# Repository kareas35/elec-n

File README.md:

# elec-n
Elektronik eğitim ve hesaplayıcılar sitesi

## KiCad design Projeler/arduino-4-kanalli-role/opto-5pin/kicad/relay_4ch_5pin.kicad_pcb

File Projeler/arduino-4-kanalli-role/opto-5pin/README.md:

# 4 Röleli Arduino Devresi — V2 / 5 Pinli (kullanıcı pin haritası)

Klasör: `C:\SalonAsistan\yatirim_takip\devre_4role_5pin_duzeltilmis`

## Pin haritası (onaylanan düzen)

**J1 — Yeni 5 pinli kontrol soketi**

| Pin | İsim | Bağlantı |
|---|---|---|
| 1 | GND | Arduino GND |
| 2 | IN1 | Arduino **D4** |
| 3 | IN2 | Arduino **D5** |
| 4 | IN3 | Arduino **D6** |
| 5 | IN4 | Arduino **D7** |

**J2 — Tek röle besleme girişi**

| Pin | Bağlantı |
|---|---|
| 1 | Harici **+5 V DC** |
| 2 | GND |

J1'de **5V yoktur**. Arduino yalnızca USB'den beslenir. J2'den gelen +5V yalnızca röle bobinlerini besler; Arduino'ya verilmez. Eski 6 pinli sürümde +5V header'daydı ve iki 5V birbirine karışıyordu; bu sürümde o pin kaldırıldı.

## Devre özeti (her kanal)

- Arduino `D4–D7` → **1 kΩ** → PC817 giriş LED'i (pin 1) → pin 2 → `GND_A`
- PC817 çıkışı: pin 4 → `+5V_B`, pin 3 → `B{k}` → **4k7** → `GND_B`
- `B{k}` → **BC547** tabanı; kollektör → röle bobini → `+5V_B`
- Bobin üzerinde **1N4148** flyback diyot
- Röle kontağı **COM / NO** → yük terminali `J{k+2}` (J3–J6)
- Filtre: J2 `+5V_B` için **100 µF + 100 nF**
- Mantık: Arduino `HIGH` → röle çekilir → COM-NO kapanır
- PC817 optokuplörleri sayesinde `GND_A` (Arduino) ve `GND_B` (röle) ayrıdır; PCB'de **X = 64.5–67.0 mm** bakırsız bariyer vardır.

> Wokwi'de optokuplör bileşeni olmadığı için simülasyonda GND'ler ortak gösterilmiştir. Gerçek PCB'de ayrıdır.

## Dosyalar

| Yol | İçerik |
|---|---|
| `kicad/relay_4ch_5pin.kicad_pro` | KiCad 10 projesi |
| `kicad/relay_4ch_5pin.kicad_sch` | Şema (J1 5 pin, J2 tek besleme) |
| `kicad/relay_4ch_5pin.kicad_pcb` | 2 katman PCB, izolasyon bariyerli |
| `kicad/design.py`, `gen_sch.py`, `gen_pcb.py` | Tek kaynaklı üretim betikleri |
| `kicad/cikti/sema.png`, `.svg`, `.pdf` | Şema çıktıları |
| `kicad/cikti/pcb.png`, `.svg` | PCB görünümü |
| `kicad/cikti/3d_ust.png`, `3d_izometrik.png` | 3B render'lar |
| `kicad/cikti/bom.csv` | Malzeme listesi |
| `sim/sketch.ino` | Arduino kodu (D4–D7) |
| `sim/diagram.json`, `wokwi.toml` | Wokwi simülasyon projesi |
| `sim/simulasyon.html` | İnternetsiz, tarayıcıda çalışan canlı simülasyon |
| `sim/build_sim.py` | `sketch.ino` → HTML içine gömer |
| `gorsel/index.html` | Tüm çıktıların görsel özet sayfası |
| `gorsel/varliklar/` | Galerinin kullandığı şema/PCB/3B/simülasyon kopyaları |
| `gorsel/hazirla.py` | Kaynak dosyaları `gorsel/varliklar/` içine kopyalar |
| `gorsel/simulasyon.gif` | Çalışan simülasyonun kaydı |

## Simülasyonu çalıştırma

1. **Tarayıcı (internetsiz):** `sim\simulasyon.html` dosyasına çift tıkla. `sketch.ino` içine gömülü olduğu için aynı kod çalışır. Hız etiketine tıklayarak 1/2/4/8x arasında geçiş yapılır.
2. **Wokwi:** `https://wokwi.com` → *New Arduino Uno Project* → `diagram.json` ve `sketch.ino` içeriklerini yapıştır → *Start simulation*.
3. **Görsel özet:** `gorsel\index.html` dosyasını aç.

## Arduino seri komutları

| Komut | Etki |
|---|---|
| `a` | 4 röleyi aç |
| `k` | 4 röleyi kapat |
| `1`–`4` | İlgili röleyi aç/kapat (toggle) |
| `s` | Durumları yazdır |

Otomatik demo: 4 açık (1.5 s) → 4 kapalı (0.9 s) → sırayla R1…R4 (0.6 s açık / 0.3 s kapalı) → tekrar.

## Doğrulama sonuçları

- **ERC:** 0 hata, 0 uyarı
- **DRC:** 0 ihlal
- **Router:** 32 bağlantı / 32 başarılı
- **Arduino CLI:** `arduino:avr:uno` derlemesi başarılı (3310 B flash, 224 B RAM)
- **Wokwi:** `diagram.json` geçerli, 18 parça / 32 bağlantı
- **Simülasyon:** `simulasyon.gif` ve `gorsel/sim_durum_*.png` kayıtları

## Yeniden üretim

```powershell
cd C:\SalonAsistan\yatirim_takip\devre_4role_5pin_duzeltilmis
python kicad\gen_sch.py
& 'C:\Program Files\KiCad\10.0\bin\python.exe' kicad\gen_pcb.py
& 'C:\Program Files\KiCad\10.0\bin\kicad-cli.exe' sch erc --severity-all -o kicad\erc.json --format json kicad\relay_4ch_5pin.kicad_sch
& 'C:\Program Files\KiCad\10.0\bin\kicad-cli.exe' pcb drc --severity-all -o kicad\drc.json --format json kicad\relay_4ch_5pin.kicad_pcb
python sim\build_sim.py
python sim\animasyon.py
python gorsel\hazirla.py
```

> `gorsel\index.html` dosyası şema/PCB/3B görselleri ile canlı simülasyonu kendi `varliklar\` alt klasöründen okur; dosyalar değiştiğinde `python gorsel\hazirla.py` komutunu çalıştır.

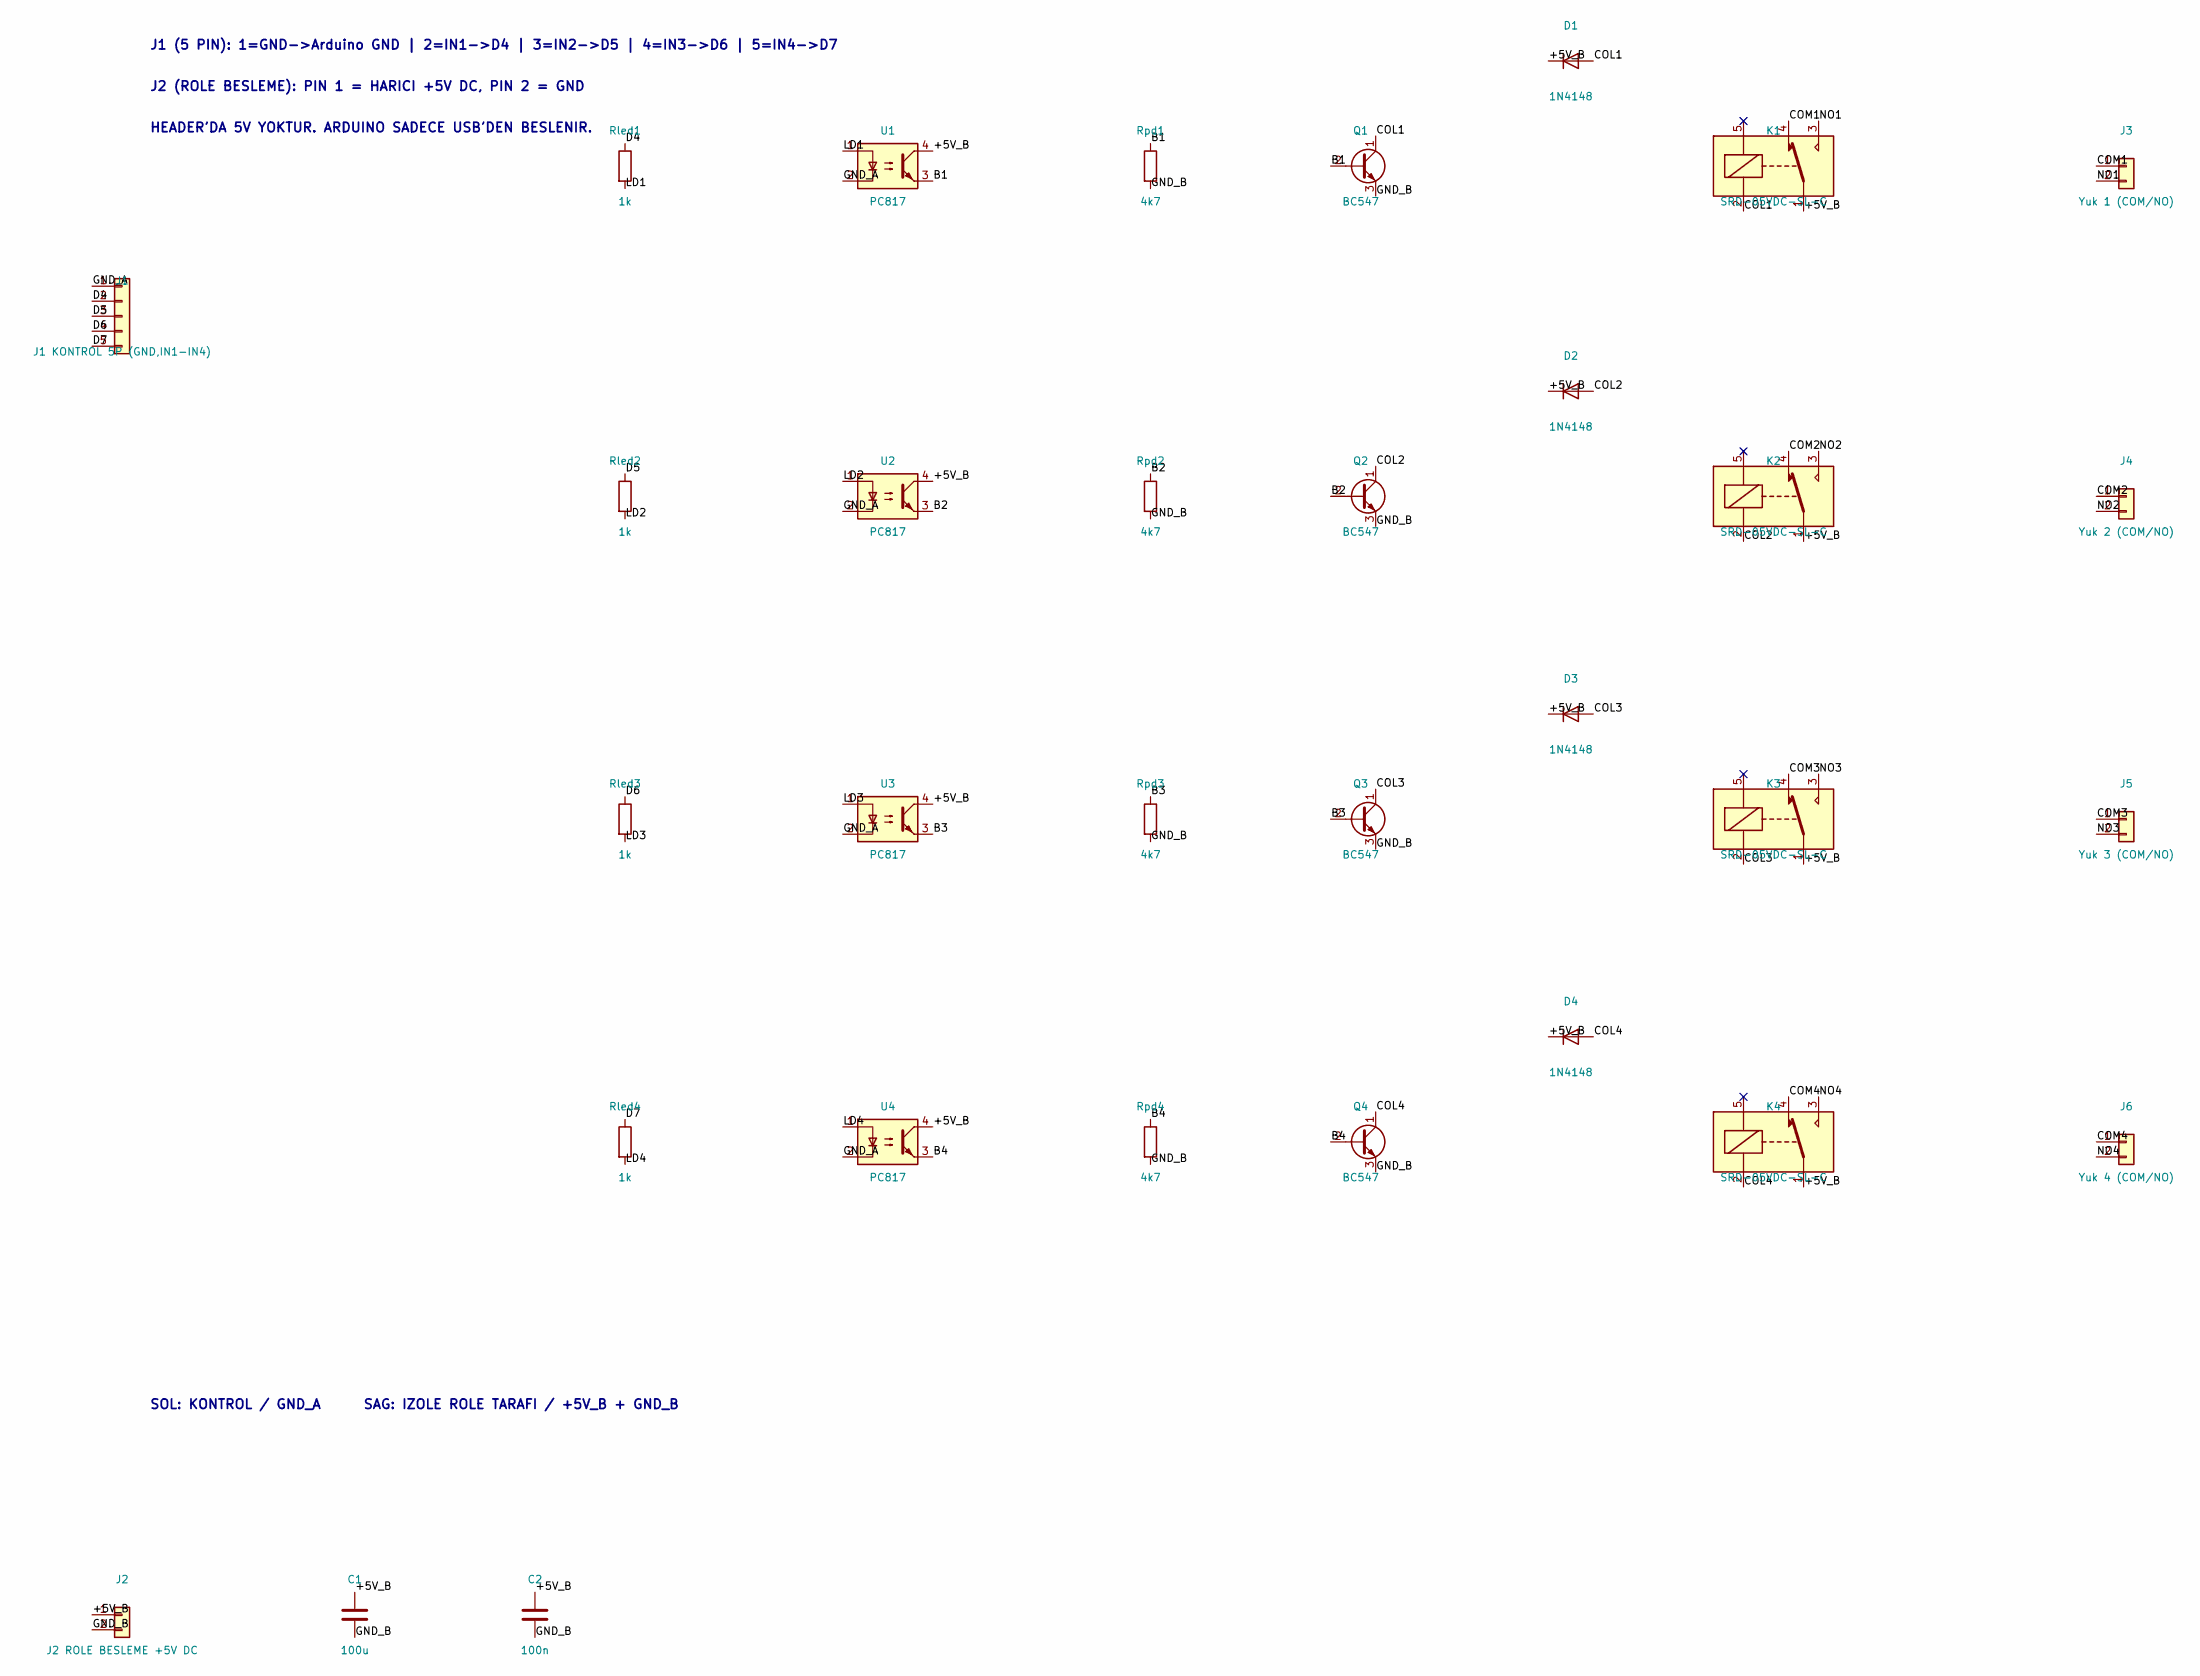
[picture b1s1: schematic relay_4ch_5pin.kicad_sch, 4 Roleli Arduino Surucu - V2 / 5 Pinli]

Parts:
C1: 100u; CP_Radial_D6.3mm_P2.50mm
C2: 100n; C_Disc_D5.0mm_W2.5mm_P5.00mm
D1, D2, D3, D4: 1N4148; D_DO-41_SOD81_P10.16mm_Horizontal
J1: J1 KONTROL 5P (GND,IN1-IN4); PinHeader_1x05_P2.54mm_Vertical
J2: J2 ROLE BESLEME +5V DC; TerminalBlock_Phoenix_MKDS-1,5-2-5.08_1x02_P5.08mm_Horizont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
J3: Yuk 1 (COM/NO); TerminalBlock_Phoenix_MKDS-1,5-2-5.08_1x02_P5.08mm_Horizont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
J4: Yuk 2 (COM/NO); TerminalBlock_Phoenix_MKDS-1,5-2-5.08_1x02_P5.08mm_Horizont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
J5: Yuk 3 (COM/NO); TerminalBlock_Phoenix_MKDS-1,5-2-5.08_1x02_P5.08mm_Horizont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
J6: Yuk 4 (COM/NO); TerminalBlock_Phoenix_MKDS-1,5-2-5.08_1x02_P5.08mm_Horizont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
K1, K2, K3, K4: SRD-05VDC-SL-C; Relay_SPDT_SANYOU_SRD_Series_Form_C
Q1, Q2, Q3, Q4: BC547; TO-92_Inline
Rled1, Rled2, Rled3, Rled4: 1k; R_Axial_DIN0207_L6.3mm_D2.5mm_P10.16mm_Horizontal
Rpd1, Rpd2, Rpd3, Rpd4: 4k7; R_Axial_DIN0207_L6.3mm_D2.5mm_P10.16mm_Horizontal
U1, U2, U3, U4: PC817; DIP-4_W7.62mm

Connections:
+5V_B: C1.1, C2.1, D1.1 (K), D2.1 (K), D3.1 (K), D4.1 (K), J2.1, K1.1, K2.1, K3.1, K4.1, U1.4, U2.4, U3.4, U4.4
B1: Q1.2 (B), Rpd1.1, U1.3
B2: Q2.2 (B), Rpd2.1, U2.3
B3: Q3.2 (B), Rpd3.1, U3.3
B4: Q4.2 (B), Rpd4.1, U4.3
COL1: D1.2 (A), K1.2, Q1.1 (C)
COL2: D2.2 (A), K2.2, Q2.1 (C)
COL3: D3.2 (A), K3.2, Q3.1 (C)
COL4: D4.2 (A), K4.2, Q4.1 (C)
COM1: J3.1, K1.4
COM2: J4.1, K2.4
COM3: J5.1, K3.4
COM4: J6.1, K4.4
D4: J1.2, Rled1.1
D5: J1.3, Rled2.1
D6: J1.4, Rled3.1
D7: J1.5, Rled4.1
GND_A: J1.1, U1.2, U2.2, U3.2, U4.2
GND_B: C1.2, C2.2, J2.2, Q1.3 (E), Q2.3 (E), Q3.3 (E), Q4.3 (E), Rpd1.2, Rpd2.2, Rpd3.2, Rpd4.2
LD1: Rled1.2, U1.1
LD2: Rled2.2, U2.1
LD3: Rled3.2, U3.1
LD4: Rled4.2, U4.1
NC1: K1.5
NC2: K2.5
NC3: K3.5
NC4: K4.5
NO1: J3.2, K1.3
NO2: J4.2, K2.3
NO3: J5.2, K3.3
NO4: J6.2, K4.3

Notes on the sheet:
J1 (5 PIN): 1=GND->Arduino GND | 2=IN1->D4 | 3=IN2->D5 | 4=IN3->D6 | 5=IN4->D7
J2 (ROLE BESLEME): PIN 1 = HARICI +5V DC, PIN 2 = GND
HEADER'DA 5V YOKTUR. ARDUINO SADECE USB'DEN BESLENIR.
SOL: KONTROL / GND_A SAG: IZOLE ROLE TARAFI / +5V_B + GND_B

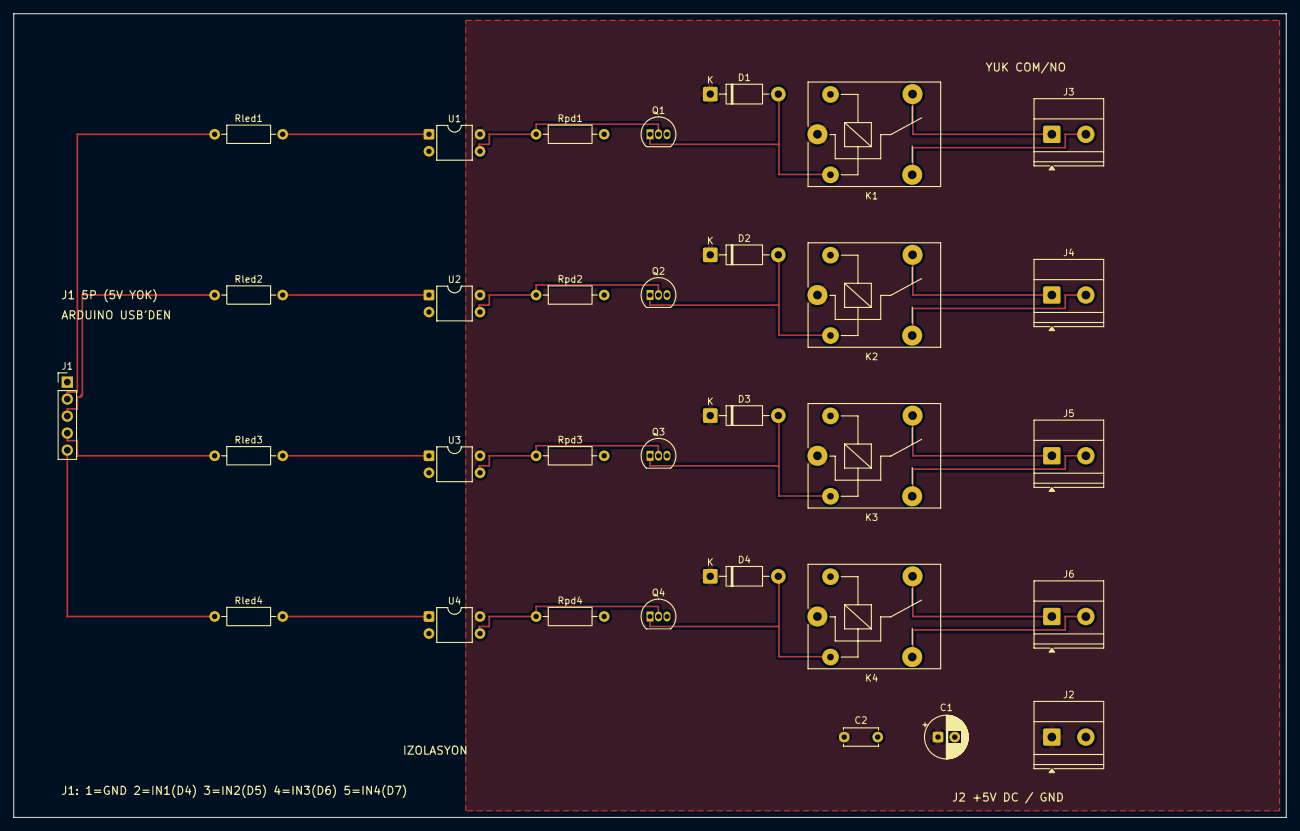
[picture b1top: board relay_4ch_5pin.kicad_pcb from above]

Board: 2 copper layers, 190.0 x 120.0 mm, 32 parts (0 on the bottom side), 27 nets.

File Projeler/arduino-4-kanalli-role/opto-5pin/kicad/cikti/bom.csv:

"Refs","Value","Footprint","Qty","DNP"
"C1","100u","Capacitor_THT:CP_Radial_D6.3mm_P2.50mm","1",""
"C2","100n","Capacitor_THT:C_Disc_D5.0mm_W2.5mm_P5.00mm","1",""
"D1","1N4148","Diode_THT:D_DO-41_SOD81_P10.16mm_Horizontal","1",""
"D2","1N4148","Diode_THT:D_DO-41_SOD81_P10.16mm_Horizontal","1",""
"D3","1N4148","Diode_THT:D_DO-41_SOD81_P10.16mm_Horizontal","1",""
"D4","1N4148","Diode_THT:D_DO-41_SOD81_P10.16mm_Horizontal","1",""
"J1","J1 KONTROL 5P (GND,IN1-IN4)","Connector_PinHeader_2.54mm:PinHeader_1x05_P2.54mm_Vertical","1",""
"J2","J2 ROLE BESLEME +5V DC","TerminalBlock_Phoenix:TerminalBlock_Phoenix_MKDS-1,5-2-5.08_1x02_P5.08mm_Horizontal","1",""
"J3","Yuk 1 (COM/NO)","TerminalBlock_Phoenix:TerminalBlock_Phoenix_MKDS-1,5-2-5.08_1x02_P5.08mm_Horizontal","1",""
"J4","Yuk 2 (COM/NO)","TerminalBlock_Phoenix:TerminalBlock_Phoenix_MKDS-1,5-2-5.08_1x02_P5.08mm_Horizontal","1",""
"J5","Yuk 3 (COM/NO)","TerminalBlock_Phoenix:TerminalBlock_Phoenix_MKDS-1,5-2-5.08_1x02_P5.08mm_Horizontal","1",""
"J6","Yuk 4 (COM/NO)","TerminalBlock_Phoenix:TerminalBlock_Phoenix_MKDS-1,5-2-5.08_1x02_P5.08mm_Horizontal","1",""
"K1","SRD-05VDC-SL-C","Relay_THT:Relay_SPDT_SANYOU_SRD_Series_Form_C","1",""
"K2","SRD-05VDC-SL-C","Relay_THT:Relay_SPDT_SANYOU_SRD_Series_Form_C","1",""
"K3","SRD-05VDC-SL-C","Relay_THT:Relay_SPDT_SANYOU_SRD_Series_Form_C","1",""
"K4","SRD-05VDC-SL-C","Relay_THT:Relay_SPDT_SANYOU_SRD_Series_Form_C","1",""
"Q1","BC547","Package_TO_SOT_THT:TO-92_Inline","1",""
"Q2","BC547","Package_TO_SOT_THT:TO-92_Inline","1",""
"Q3","BC547","Package_TO_SOT_THT:TO-92_Inline","1",""
"Q4","BC547","Package_TO_SOT_THT:TO-92_Inline","1",""
"Rled1","1k","Resistor_THT:R_Axial_DIN0207_L6.3mm_D2.5mm_P10.16mm_Horizontal","1",""
"Rled2","1k","Resistor_THT:R_Axial_DIN0207_L6.3mm_D2.5mm_P10.16mm_Horizontal","1",""
"Rled3","1k","Resistor_THT:R_Axial_DIN0207_L6.3mm_D2.5mm_P10.16mm_Horizontal","1",""
"Rled4","1k","Resistor_THT:R_Axial_DIN0207_L6.3mm_D2.5mm_P10.16mm_Horizontal","1",""
"Rpd1","4k7","Resistor_THT:R_Axial_DIN0207_L6.3mm_D2.5mm_P10.16mm_Horizontal","1",""
"Rpd2","4k7","Resistor_THT:R_Axial_DIN0207_L6.3mm_D2.5mm_P10.16mm_Horizontal","1",""
"Rpd3","4k7","Resistor_THT:R_Axial_DIN0207_L6.3mm_D2.5mm_P10.16mm_Horizontal","1",""
"Rpd4","4k7","Resistor_THT:R_Axial_DIN0207_L6.3mm_D2.5mm_P10.16mm_Horizontal","1",""
"U1","PC817","Package_DIP:DIP-4_W7.62mm","1",""
"U2","PC817","Package_DIP:DIP-4_W7.62mm","1",""
"U3","PC817","Package_DIP:DIP-4_W7.62mm","1",""
"U4","PC817","Package_DIP:DIP-4_W7.62mm","1",""

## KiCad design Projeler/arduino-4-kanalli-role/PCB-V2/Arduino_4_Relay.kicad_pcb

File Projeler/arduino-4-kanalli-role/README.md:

# 4 Kanallı Arduino Röle Kartı

Arduino Uno ile kontrol edilen, ULN2003A sürücülü, 5 V bobinli 4 kanallı röle kartı.
Şema, PCB, 3B görünüm, Gerber/drill, firmware, sayısal simülasyon ve SimulIDE
projesi bu klasörde birlikte bulunur.

> **Güvenlik — yalnızca düşük gerilimli eğitim:**
> Bu PCB'nin 230 V şebeke güvenliği doğrulanmamıştır.
> Şebeke gerilimi bağlamayın. Kontak yolları 0,5 mm'dir;
> güvenli akım kapasitesi henüz doğrulanmamıştır.
> Röleleri Arduino 5 V pininden beslemeyin.
> Harici, regüle 5 V DC kaynak kullanın.
> J2-1: +5 V, J2-2: GND.
> Arduino ve röle kartının GND bağlantısı ortak olmalıdır.
> J1-1 ve J2-1 aynı +5 V hattındadır.
> Harici besleme kullanırken J1-1'i Arduino 5 V pinine
> BAĞLAMAYIN. Mevcut PCB yanlış bağlantıyı engellemez.

## Donanım özeti

| Öğe | Değer / bağlantı |
|---|---|
| Besleme | 5 V DC. 4 röle aynı anda açıksa harici 5 V / 2 A önerilir. |
| Sürücü | ULN2003A (SOIC-16), entegre flyback diyotları |
| Röle | 4 × SRD-05VDC-SL-C, SPDT, bobin 5 V |
| Kontak çıkışı | Her kanal için COM / NO / NC vidalı terminal |
| Giriş | IN1..IN4, aktif-YÜKSEK, 10 kΩ pull-down |
| Kart boyutu | 140 × 95 mm |

### J1 — Arduino giriş soketi

| J1 pini | Sinyal | Arduino Uno |
|---:|---|---|
| 1 | +5V | Harici beslemede bağlama |
| 2 | GND | GND |
| 3 | IN1 | D4 |
| 4 | IN2 | D5 |
| 5 | IN3 | D6 |
| 6 | IN4 | D7 |

J2 isteğe bağlı harici 5 V girişidir: pin 1 +5V, pin 2 GND. J2 kullanılıyorsa
J1'in 5 V pini bağlanmaz; GND ortak kalır.

### J3..J6 — röle çıkış terminalleri

| Terminal pini | Kontak |
|---:|---|
| 1 | COM |
| 2 | NO (enerjiliyken kapalı) |
| 3 | NC (enerjisizken kapalı) |

Kart üzerindeki D1..D4 LED'leri ULN çıkışlarını, yani kanalın aktif olduğunu
gösterir. SimulIDE ekranındaki LED'ler ise röle kontaklarının kapandığını
göstermek için NO çıkışına eklenmiş ayrı 330 Ω + LED yükleridir.

## Yazılım davranışı

`Arduino_4_Relay/firmware/Arduino_4_Relay/Arduino_4_Relay.ino`:

1. Açılışta 4 kanal da kapatılır.
2. Kanal 1→4 sırayla 0,5 s açılır.
3. Tüm kanallar 0,5 s açık, 1 s kapalı kalır.
4. 8 adımlı kovalamaca dizisi (0,25 s/adım) çalışır.
5. 2 s bekleme sonrası döngü tekrar eder.

Derlenen çıktı: `Arduino_4_Relay.ino.hex` (2432 bayt flash, 252 bayt RAM).

## Dosyalar

```
Arduino_4_Relay/
├─ Arduino_4_Relay.kicad_sch        Şematik
├─ Arduino_4_Relay.kicad_pcb        PCB
├─ netlist.net                      Doğrulanmış KiCad netlist'i
├─ erc.rpt / drc.rpt                0 hata / 0 uyarı raporları
├─ firmware/
│  ├─ Arduino_4_Relay/Arduino_4_Relay.ino
│  └─ Arduino_4_Relay.ino.hex       SimulIDE'ye yüklenen firmware
├─ simulation/
│  ├─ transient.csv / transient.png / animation.gif
│  ├─ relay4_arduino.cir            ngspice uyumlu devre dosyası
│  └─ simulide/
│     ├─ Arduino_4_Relay.sim1       Arduino kodu yüklü proje
│     └─ Arduino_4_Relay.ino.hex
├─ docs/
│  ├─ Arduino_4_Relay_schematic.pdf / .svg
│  ├─ Arduino_4_Relay_pcb_layers.svg
│  ├─ pcb_3d.png
│  ├─ bom.csv
│  └─ simulide_running.png         Simülasyon çalışırken ekran görüntüsü
└─ gerber/                          Gerber + Excellon drill dosyaları
```

## Yeniden üretim

Tüm komutlar proje kökünde (`Varsayılan Proje`) çalıştırılır.

```powershell
# Şema, netlist, ERC, PCB ve DRC
python scripts\build_all.py
python scripts\validate_netlist.py

# PDF/SVG/BOM/Gerber/drill/3B render
python scripts\export_docs.py

# Arduino firmware derleme
& "C:\Program Files\Arduino CLI\arduino-cli.exe" compile `
  --fqbn arduino:avr:uno --output-dir Arduino_4_Relay\firmware `
  Arduino_4_Relay\firmware\Arduino_4_Relay

# Geçici rejim simülasyonu (scipy + matplotlib gerekir)
python scripts\simulate.py

# SimulIDE projesini HEX ile yenile
python scripts\simulide.py
```

`build_all.py`, PCB adımı için KiCad'in kendi Python'unu
(`C:\Program Files\KiCad\10.0\bin\python.exe`) kullanır; diğer adımlar normal
Python ile çalışır.

Gerekli yazılımlar: KiCad 10.0.8, Arduino CLI 1.6.0 (`arduino:avr:uno` çekirdeği),
SimulIDE 1.1.0 ve Python 3 (`numpy`, `scipy`, `matplotlib`, `Pillow`).

## SimulIDE'de çalıştırma

1. `Arduino_4_Relay\simulation\simulide\Arduino_4_Relay.sim1` dosyasını açın.
   Klasör adındaki Türkçe karakter nedeniyle sorun olursa, klasöre ASCII bir
   sürücü harfi atayın: `subst S: " ... \Arduino_4_Relay\simulation\simulide"`
   ve `S:\Arduino_4_Relay.sim1` dosyasını açın.
2. Üst araç çubuğundaki **Off** düğmesine basın; simülasyon başlar ve HEX
   dosyası otomatik olarak yeniden yüklenir.
3. Arduino kodu D4..D7'yi sırayla değiştirdikçe ULN çıkışları, röle bobinleri
   ve NO kontaklarına bağlı LED'ler yanar. `docs\simulide_running.png` tüm
   kanalların açık olduğu andan alınmıştır.

Son doğrulama: netlist geçerli, ERC 0/0, DRC 0/0, firmware derlendi, transient
simülasyonu ve SimulIDE çalışması tamamlandı.

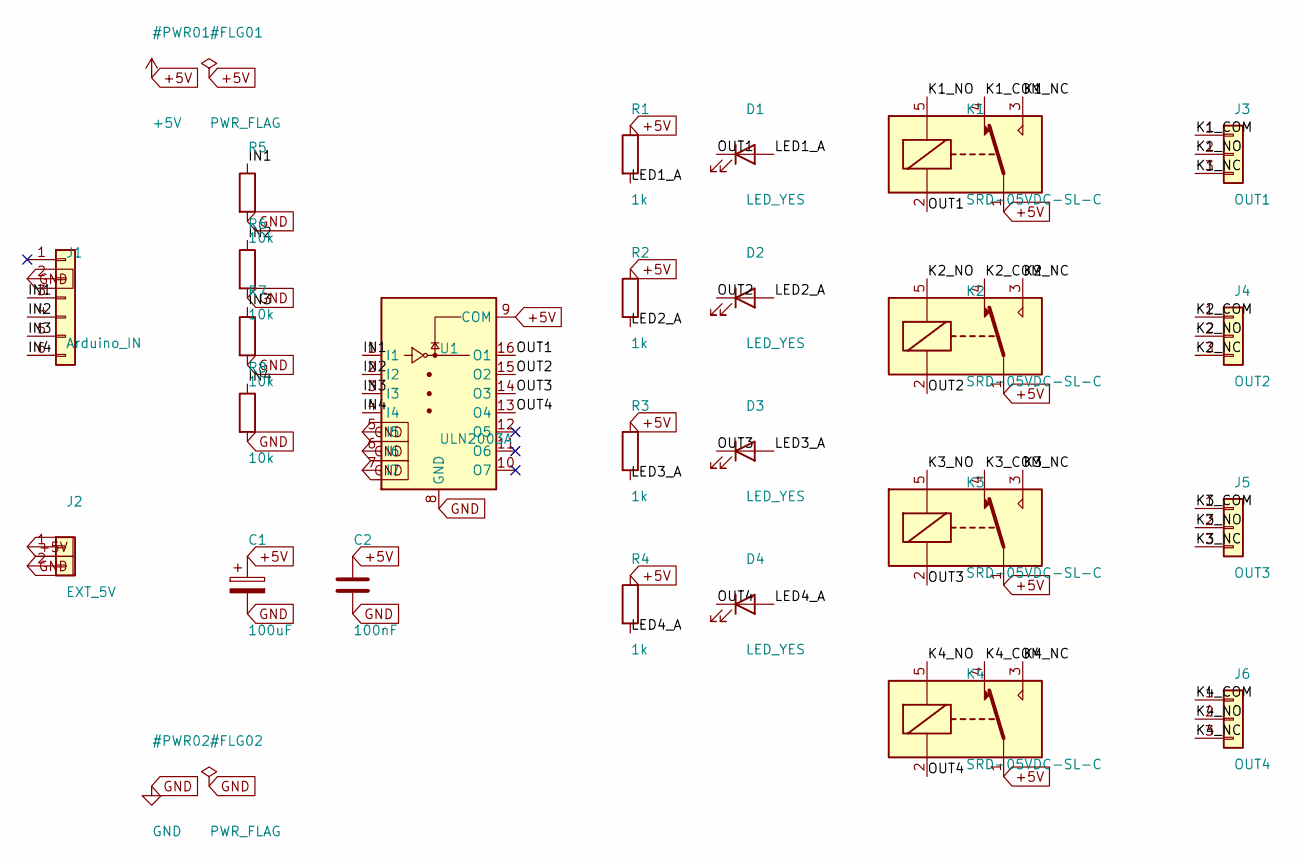
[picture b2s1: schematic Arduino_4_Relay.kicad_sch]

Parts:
C1: 100uF; CP_Radial_D5.0mm_P2.00mm
C2: 100nF; C_Disc_D5.0mm_W2.5mm_P5.00mm
D1, D2, D3, D4: LED_YES; LED_D5.0mm
J1: Arduino_IN; PinHeader_1x06_P2.54mm_Vertical
J2: EXT_5V; PinHeader_1x02_P2.54mm_Vertical
J3: OUT1; TerminalBlock_Phoenix_MKDS-1,5-3-5.08_1x03_P5.08mm_Horizont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
J4: OUT2; TerminalBlock_Phoenix_MKDS-1,5-3-5.08_1x03_P5.08mm_Horizont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
J5: OUT3; TerminalBlock_Phoenix_MKDS-1,5-3-5.08_1x03_P5.08mm_Horizont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
J6: OUT4; TerminalBlock_Phoenix_MKDS-1,5-3-5.08_1x03_P5.08mm_Horizont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
K1, K2, K3, K4: SRD-05VDC-SL-C; Relay_SPDT_SANYOU_SRD_Series_Form_C
R1, R2, R3, R4: 1k; R_Axial_DIN0207_L6.3mm_D2.5mm_P7.62mm_Horizontal
R5, R6, R7, R8: 10k; R_Axial_DIN0207_L6.3mm_D2.5mm_P7.62mm_Horizontal
U1: ULN2003A; SOIC-16_3.9x9.9mm_P1.27mm

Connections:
+5V: C1.1, C2.1, J2.1, K1.1, K2.1, K3.1, K4.1, R1.1, R2.1, R3.1, R4.1, U1.9 (COM)
GND: C1.2, C2.2, J1.2, J2.2, R5.2, R6.2, R7.2, R8.2, U1.5 (I5), U1.6 (I6), U1.7 (I7), U1.8 (GND)
IN1: J1.3, R5.1, U1.1 (I1)
IN2: J1.4, R6.1, U1.2 (I2)
IN3: J1.5, R7.1, U1.3 (I3)
IN4: J1.6, R8.1, U1.4 (I4)
K1_COM: J3.1, K1.4
K1_NC: J3.3, K1.3
K1_NO: J3.2, K1.5
K2_COM: J4.1, K2.4
K2_NC: J4.3, K2.3
K2_NO: J4.2, K2.5
K3_COM: J5.1, K3.4
K3_NC: J5.3, K3.3
K3_NO: J5.2, K3.5
K4_COM: J6.1, K4.4
K4_NC: J6.3, K4.3
K4_NO: J6.2, K4.5
LED1_A: D1.2 (A), R1.2
LED2_A: D2.2 (A), R2.2
LED3_A: D3.2 (A), R3.2
LED4_A: D4.2 (A), R4.2
OUT1: D1.1 (K), K1.2, U1.16 (O1)
OUT2: D2.1 (K), K2.2, U1.15 (O2)
OUT3: D3.1 (K), K3.2, U1.14 (O3)
OUT4: D4.1 (K), K4.2, U1.13 (O4)

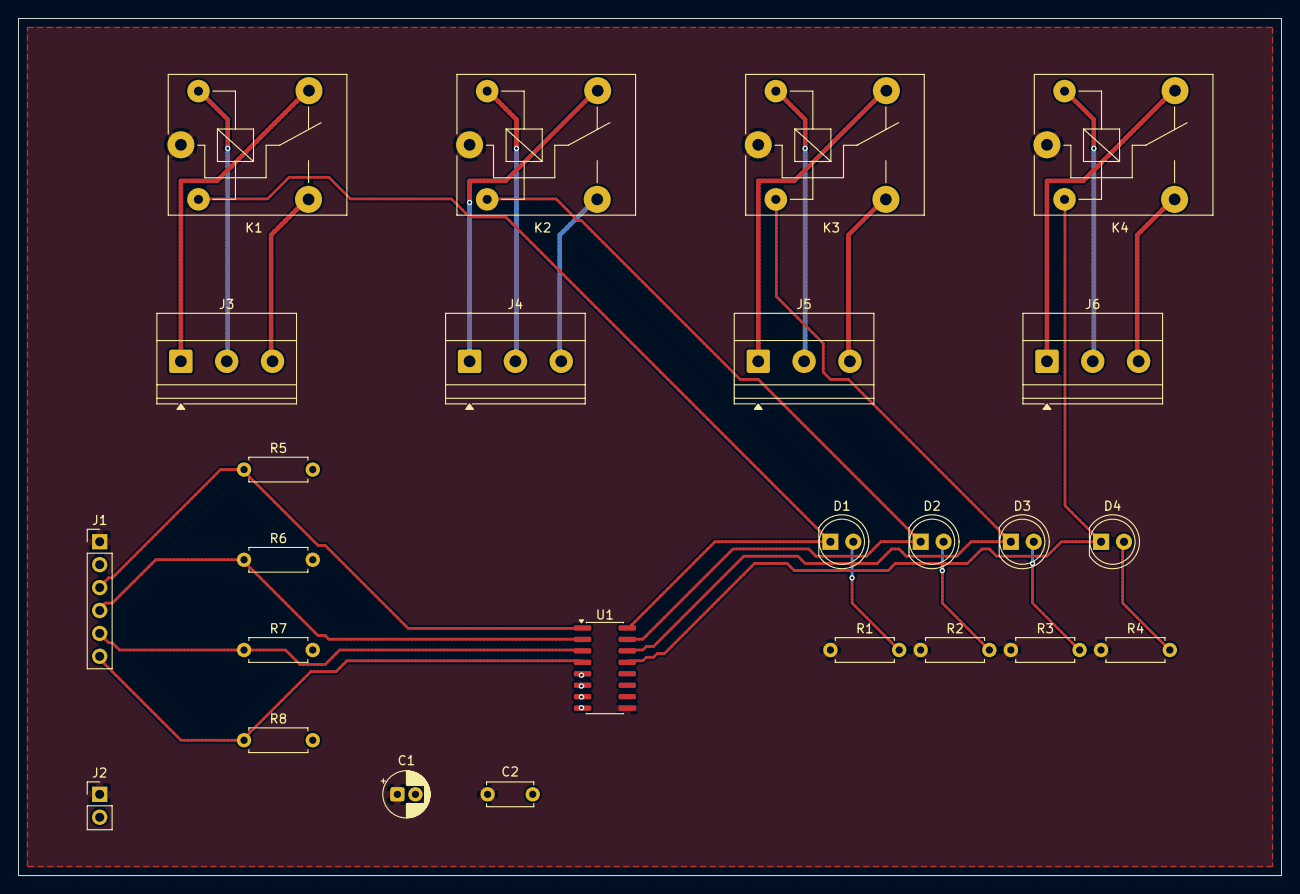
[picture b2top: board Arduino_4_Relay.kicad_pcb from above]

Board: 2 copper layers, 140.0 x 95.0 mm, 25 parts (0 on the bottom side), 26 nets.

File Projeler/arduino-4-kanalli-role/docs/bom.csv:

"Refs","Value","Footprint","Qty","DNP"
"C1","100uF","Capacitor_THT:CP_Radial_D5.0mm_P2.00mm","1",""
"C2","100nF","Capacitor_THT:C_Disc_D5.0mm_W2.5mm_P5.00mm","1",""
"D1","LED_YES","LED_THT:LED_D5.0mm","1",""
"D2","LED_YES","LED_THT:LED_D5.0mm","1",""
"D3","LED_YES","LED_THT:LED_D5.0mm","1",""
"D4","LED_YES","LED_THT:LED_D5.0mm","1",""
"J1","Arduino_IN","Connector_PinHeader_2.54mm:PinHeader_1x06_P2.54mm_Vertical","1",""
"J2","EXT_5V","Connector_PinHeader_2.54mm:PinHeader_1x02_P2.54mm_Vertical","1",""
"J3","OUT1","TerminalBlock_Phoenix:TerminalBlock_Phoenix_MKDS-1,5-3-5.08_1x03_P5.08mm_Horizontal","1",""
"J4","OUT2","TerminalBlock_Phoenix:TerminalBlock_Phoenix_MKDS-1,5-3-5.08_1x03_P5.08mm_Horizontal","1",""
"J5","OUT3","TerminalBlock_Phoenix:TerminalBlock_Phoenix_MKDS-1,5-3-5.08_1x03_P5.08mm_Horizontal","1",""
"J6","OUT4","TerminalBlock_Phoenix:TerminalBlock_Phoenix_MKDS-1,5-3-5.08_1x03_P5.08mm_Horizontal","1",""
"K1","SRD-05VDC-SL-C","Relay_THT:Relay_SPDT_SANYOU_SRD_Series_Form_C","1",""
"K2","SRD-05VDC-SL-C","Relay_THT:Relay_SPDT_SANYOU_SRD_Series_Form_C","1",""
"K3","SRD-05VDC-SL-C","Relay_THT:Relay_SPDT_SANYOU_SRD_Series_Form_C","1",""
"K4","SRD-05VDC-SL-C","Relay_THT:Relay_SPDT_SANYOU_SRD_Series_Form_C","1",""
"R1","1k","Resistor_THT:R_Axial_DIN0207_L6.3mm_D2.5mm_P7.62mm_Horizontal","1",""
"R2","1k","Resistor_THT:R_Axial_DIN0207_L6.3mm_D2.5mm_P7.62mm_Horizontal","1",""
"R3","1k","Resistor_THT:R_Axial_DIN0207_L6.3mm_D2.5mm_P7.62mm_Horizontal","1",""
"R4","1k","Resistor_THT:R_Axial_DIN0207_L6.3mm_D2.5mm_P7.62mm_Horizontal","1",""
"R5","10k","Resistor_THT:R_Axial_DIN0207_L6.3mm_D2.5mm_P7.62mm_Horizontal","1",""
"R6","10k","Resistor_THT:R_Axial_DIN0207_L6.3mm_D2.5mm_P7.62mm_Horizontal","1",""
"R7","10k","Resistor_THT:R_Axial_DIN0207_L6.3mm_D2.5mm_P7.62mm_Horizontal","1",""
"R8","10k","Resistor_THT:R_Axial_DIN0207_L6.3mm_D2.5mm_P7.62mm_Horizontal","1",""
"U1","ULN2003A","Package_SO:SOIC-16_3.9x9.9mm_P1.27mm","1",""
